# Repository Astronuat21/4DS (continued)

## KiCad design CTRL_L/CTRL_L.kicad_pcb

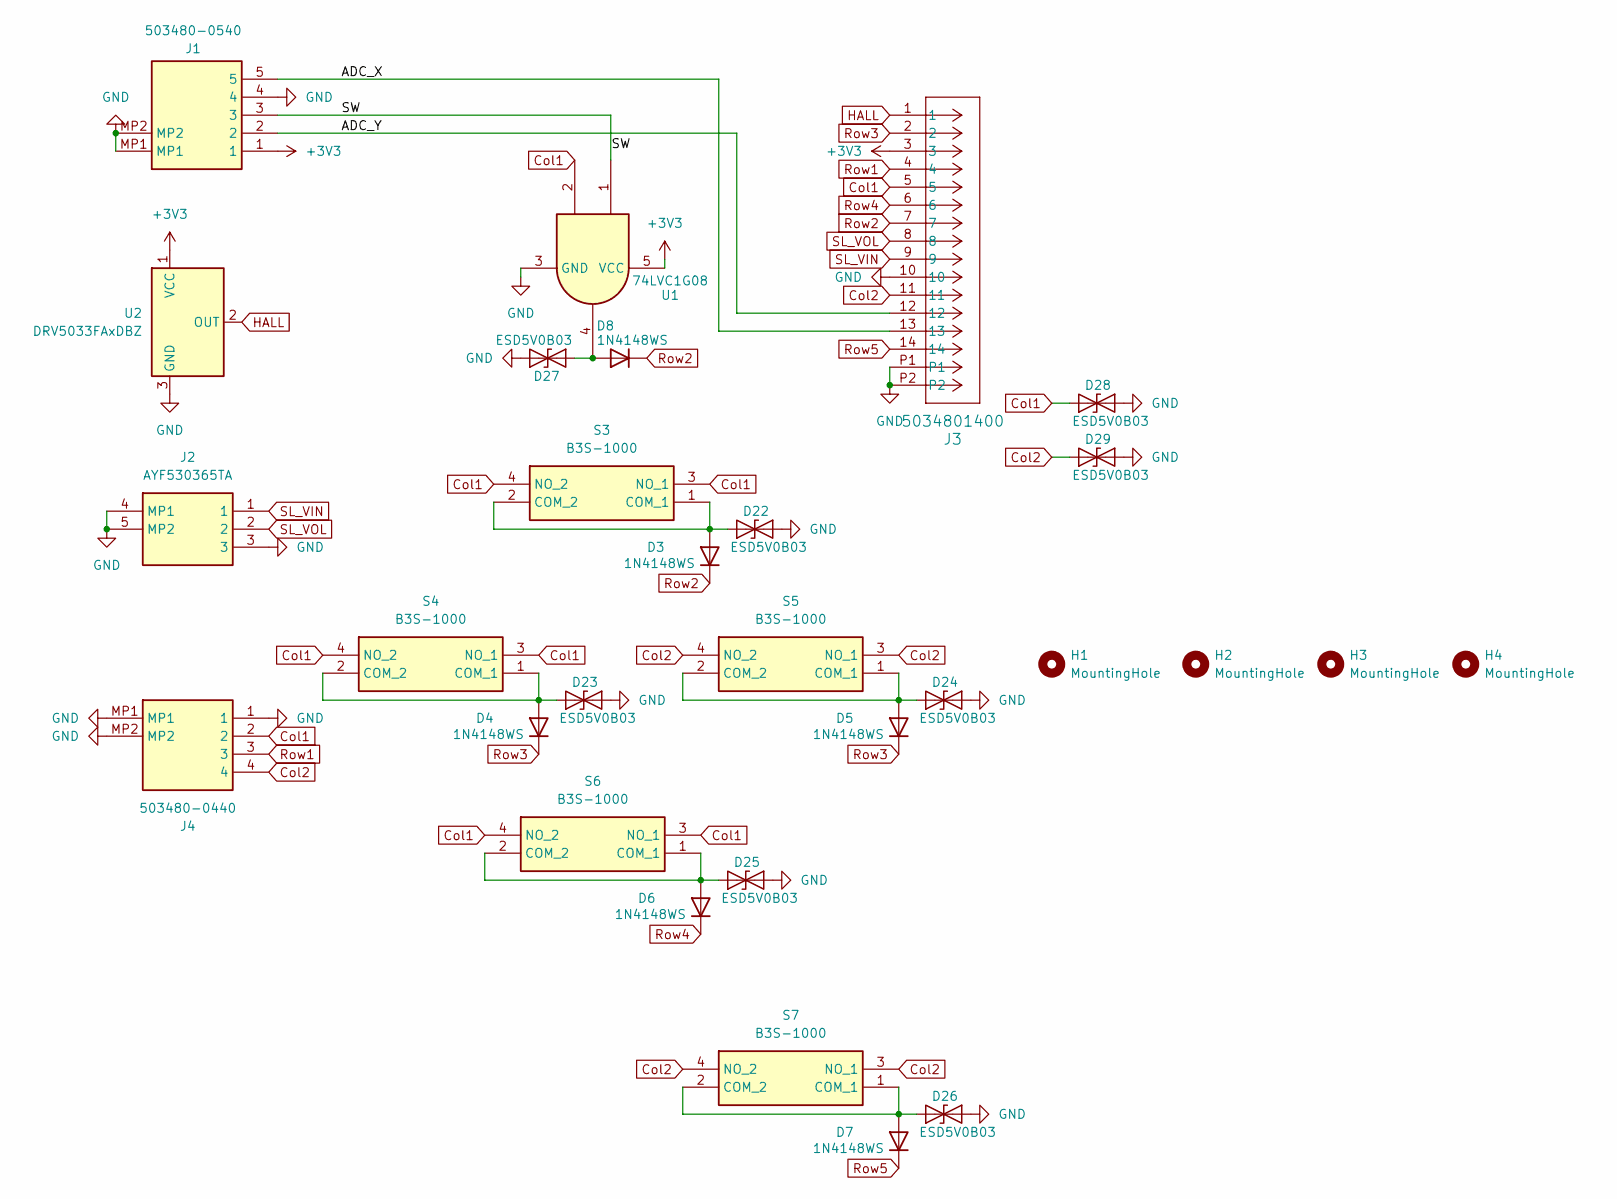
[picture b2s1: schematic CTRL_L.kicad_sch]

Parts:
D3, D4, D5, D6, D7, D8: 1N4148WS; D_SOD-323; MPN 1N4148WS; LCSC Part C917117
D22, D23, D24, D25, D26, D27, D28, D29: ESD5V0B03; D_0402_1005Metric; MPN ESD5V0B03-1006; LCSC Part C521894
H1, H2, H3, H4: MountingHole; MountingHole_2.7mm_M2.5; LCSC Part N/A
J1: 503480-0540; 5034800540; Mouser Part Number 538-503480-0540
J2: AYF530365TA; AYF530365T; Mouser Part Number 667-AYF530365TA
J3: 5034801400; MPN 5034801400; LCSC Part C505360
J4: 503480-0440; 5034800440; Mouser Part Number 538-503480-0440
S3, S4, S5, S6, S7: B3S-1000; B3S1000; Mouser Part Number 653-B3S-1000
U1: 74LVC1G08; SOT-23-5; MPN 74LVC1G08GV; LCSC Part C53185136
U2: DRV5033FAxDBZ; SOT-23; MPN DRV5033FAQDBZR; LCSC Part C2869057

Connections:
+3V3: J1.1, J3.3, U1.5 (VCC), U2.1 (VCC)
/ADC_X: J1.5, J3.13
/ADC_Y: J1.2, J3.12
/SW: J1.3, U1.1
Col1: D28.2 (A2), J3.5, J4.2, S3.3 (NO_1), S3.4 (NO_2), S4.3 (NO_1), S4.4 (NO_2), S6.3 (NO_1), S6.4 (NO_2), U1.2
Col2: D29.2 (A2), J3.11, J4.4, S5.3 (NO_1), S5.4 (NO_2), S7.3 (NO_1), S7.4 (NO_2)
GND: D22.1 (A1), D23.1 (A1), D24.1 (A1), D25.1 (A1), D26.1 (A1), D27.1 (A1), D28.1 (A1), D29.1 (A1), J1.4, J1.MP1, J1.MP2, J2.3, J2.4 (MP1), J2.5 (MP2), J3.10, J3.P1, J3.P2, J4.1, J4.MP1, J4.MP2, U1.3 (GND), U2.3 (GND)
HALL: J3.1, U2.2 (OUT)
unnamed: D3.2 (A), D22.2 (A2), S3.1 (COM_1), S3.2 (COM_2)
unnamed: D4.2 (A), D23.2 (A2), S4.1 (COM_1), S4.2 (COM_2)
unnamed: D5.2 (A), D24.2 (A2), S5.1 (COM_1), S5.2 (COM_2)
unnamed: D6.2 (A), D25.2 (A2), S6.1 (COM_1), S6.2 (COM_2)
unnamed: D7.2 (A), D26.2 (A2), S7.1 (COM_1), S7.2 (COM_2)
unnamed: D8.2 (A), D27.2 (A2), U1.4
Row1: J3.4, J4.3
Row2: D3.1 (K), D8.1 (K), J3.7
Row3: D4.1 (K), D5.1 (K), J3.2
Row4: D6.1 (K), J3.6
Row5: D7.1 (K), J3.14
SL_VIN: J2.1, J3.9
SL_VOL: J2.2, J3.8

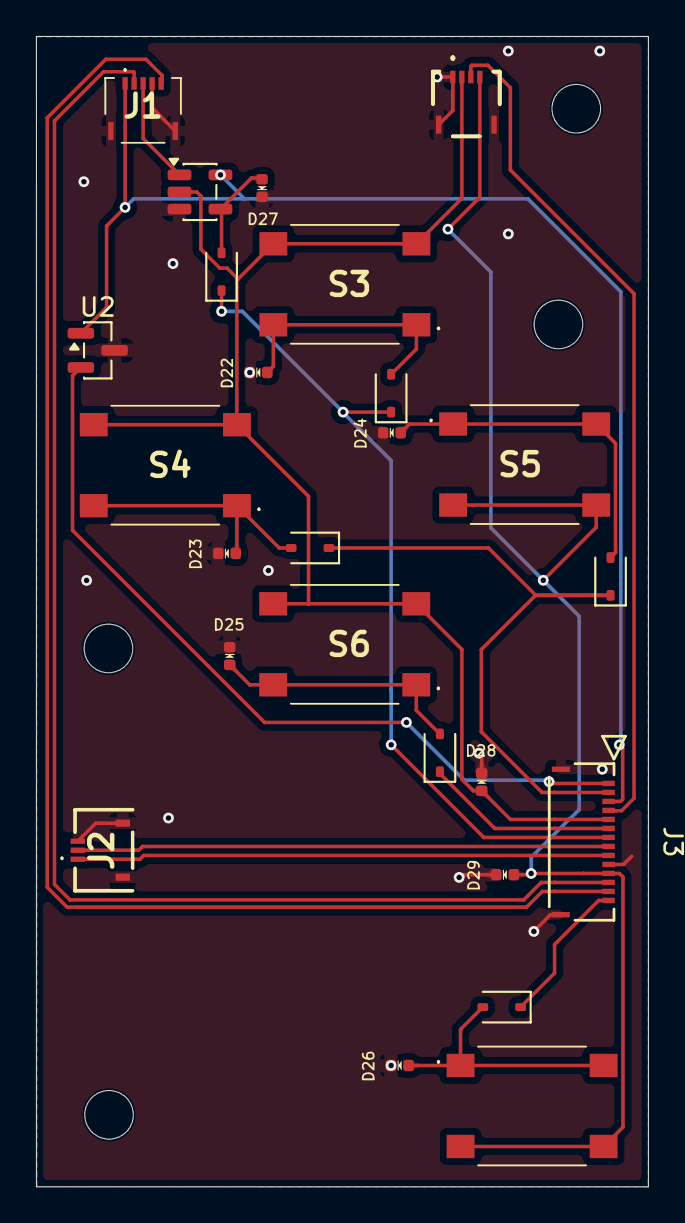
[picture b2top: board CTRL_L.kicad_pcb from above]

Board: 2 copper layers, 34.0 x 63.9 mm, 31 parts (2 on the bottom side), 21 nets.

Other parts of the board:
kibuzzard-6A186FEC: G***; kibuzzard-6A186FEC
kibuzzard-6A187131: G***; kibuzzard-6A187131

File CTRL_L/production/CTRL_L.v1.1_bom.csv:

Designator,Footprint,Quantity,Value,LCSC Part #
"D22, D23, D24, D25, D26, D27, D28, D29",0402,8,ESD5V0B03,C521894
"D3, D4, D5, D6, D7, D8",D_SOD-323,6,1N4148WS,
J2,AYF530365T,1,AYF530365TA,
J3,5034801400,1,5034801400,
J4,5034800440,1,503480-0440,
KIBUZZARD-6A186FEC,kibuzzard-6A186FEC,1,G***,
"S3, S4, S5, S6, S7",B3S1000,5,B3S-1000,
U1,SOT-23-5,1,74LVC1G08,
U2,SOT-23,1,DRV5033FAxDBZ,

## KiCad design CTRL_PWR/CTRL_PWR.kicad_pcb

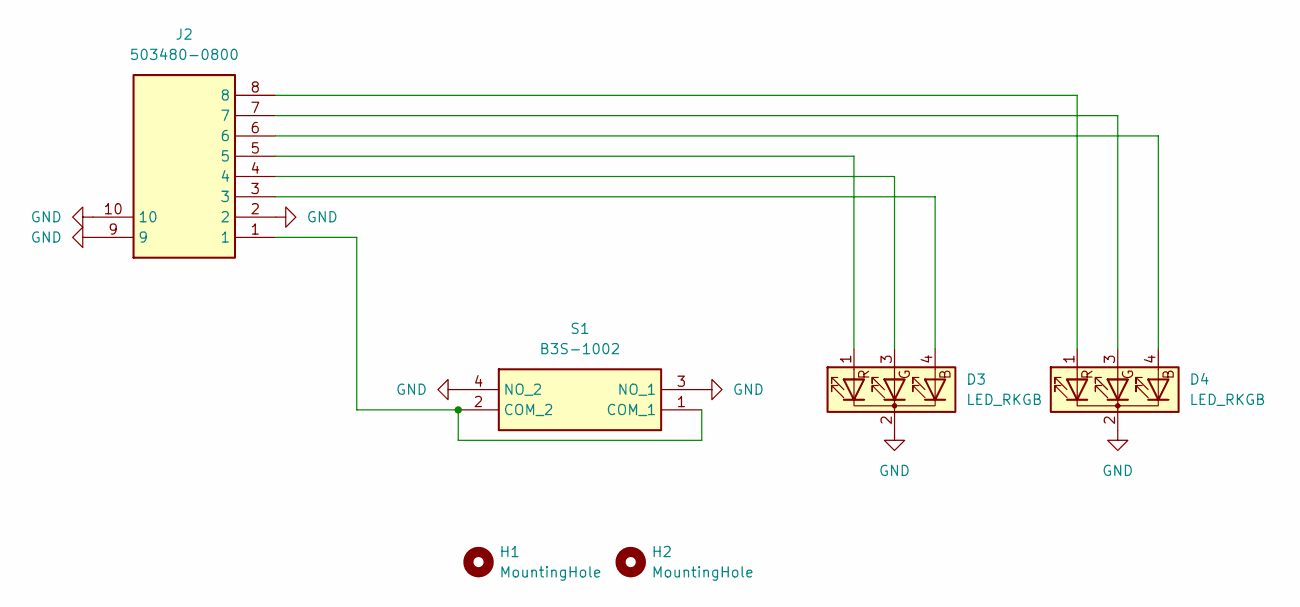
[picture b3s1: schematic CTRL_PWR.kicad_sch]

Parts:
D3, D4: LED_RKGB; LED_D5.0mm-4_RGB; MPN TJ-L5FCMXHTCSLCRGB-A5; LCSC Part C2837020
H1, H2: MountingHole; MountingHole_2.7mm_M2.5; LCSC Part N/A
J2: 503480-0800; 5034800800; Manufacturer_Part_Number 503480-0800
S1: B3S-1002; B3S1002; MPN B3S-1002; LCSC Part C2733654

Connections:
GND: D3.2 (K), D4.2 (K), J2.2, J2.9, J2.10, S1.3 (NO_1), S1.4 (NO_2)
unnamed: D3.4 (BA), J2.3
unnamed: D3.3 (GA), J2.4
unnamed: D3.1 (RA), J2.5
unnamed: D4.4 (BA), J2.6
unnamed: D4.3 (GA), J2.7
unnamed: D4.1 (RA), J2.8
unnamed: J2.1, S1.1 (COM_1), S1.2 (COM_2)

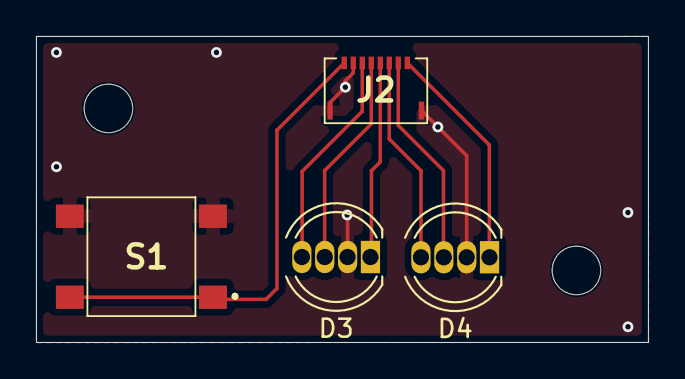
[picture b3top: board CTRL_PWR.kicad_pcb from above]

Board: 2 copper layers, 34.0 x 17.0 mm, 6 parts (0 on the bottom side), 8 nets.

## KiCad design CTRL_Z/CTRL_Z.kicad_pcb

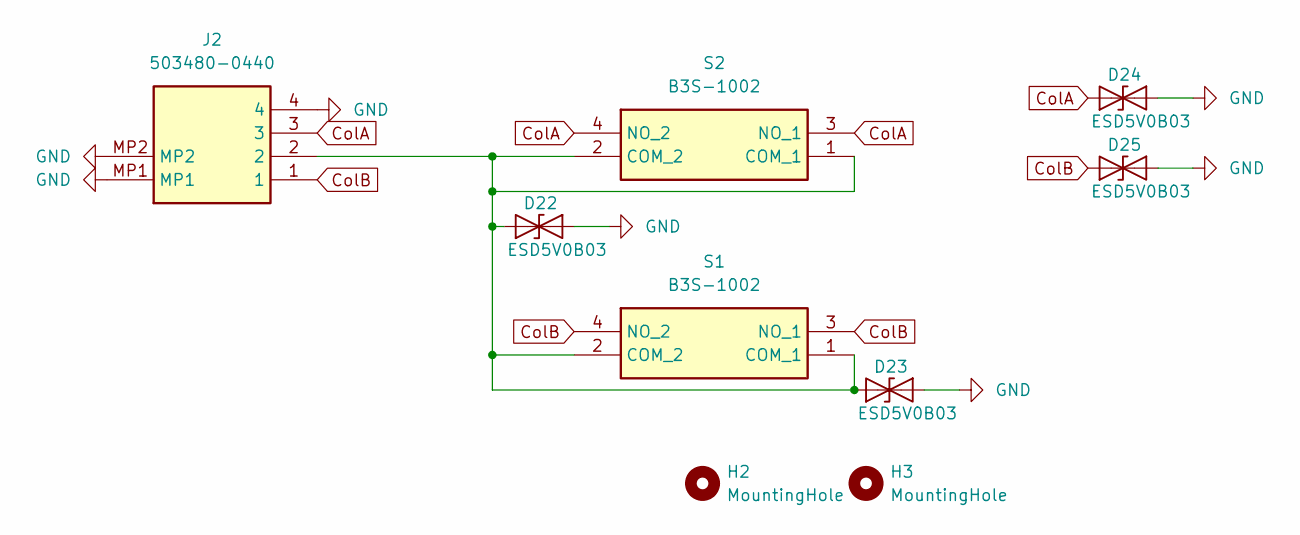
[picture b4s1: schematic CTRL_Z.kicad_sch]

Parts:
D22, D23, D24, D25: ESD5V0B03; D_0402_1005Metric; MPN ESD5V0B03-1006; LCSC Part C521894
H2, H3: MountingHole; MountingHole_2.5mm; LCSC Part N/A
J2: 503480-0440; 5034800440; Mouser Part Number 538-503480-0440
S1, S2: B3S-1002; B3S1002; Mouser Part Number 653-B3S-1002

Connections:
ColA: D24.2 (A2), J2.3, S2.3 (NO_1), S2.4 (NO_2)
ColB: D25.2 (A2), J2.1, S1.3 (NO_1), S1.4 (NO_2)
GND: D22.1 (A1), D23.1 (A1), D24.1 (A1), D25.1 (A1), J2.4, J2.MP1, J2.MP2
unnamed: D22.2 (A2), D23.2 (A2), J2.2, S1.1 (COM_1), S1.2 (COM_2), S2.1 (COM_1), S2.2 (COM_2)

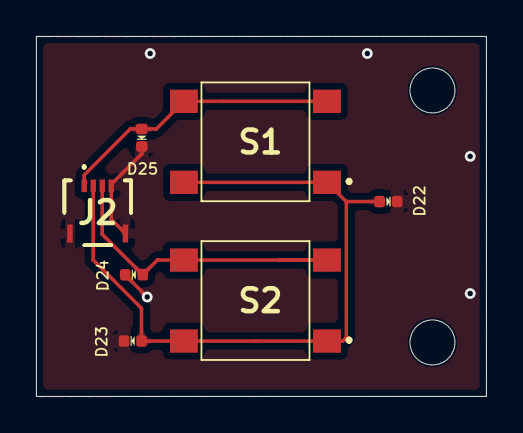
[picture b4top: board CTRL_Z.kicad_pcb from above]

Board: 2 copper layers, 25.0 x 20.0 mm, 10 parts (1 on the bottom side), 4 nets.

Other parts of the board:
kibuzzard-6A70E37C: G***; kibuzzard-6A70E37C

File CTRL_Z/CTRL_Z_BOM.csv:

"Reference","Qty","Value","Footprint","MPN","Manufacturer"
"D22,D23,D24,D25","4","ESD5V0B03","A_HDJ_Library:D_0402_1005Metric","ESD5V0B03-1006","TECH PUBLIC"
"J2","1","503480-0440","503480-0440:5034800440","5034800440","MOLEX"
"S1,S2","2","B3S-1002","B3S-1002:B3S1002","B3S-1002","OMRON"

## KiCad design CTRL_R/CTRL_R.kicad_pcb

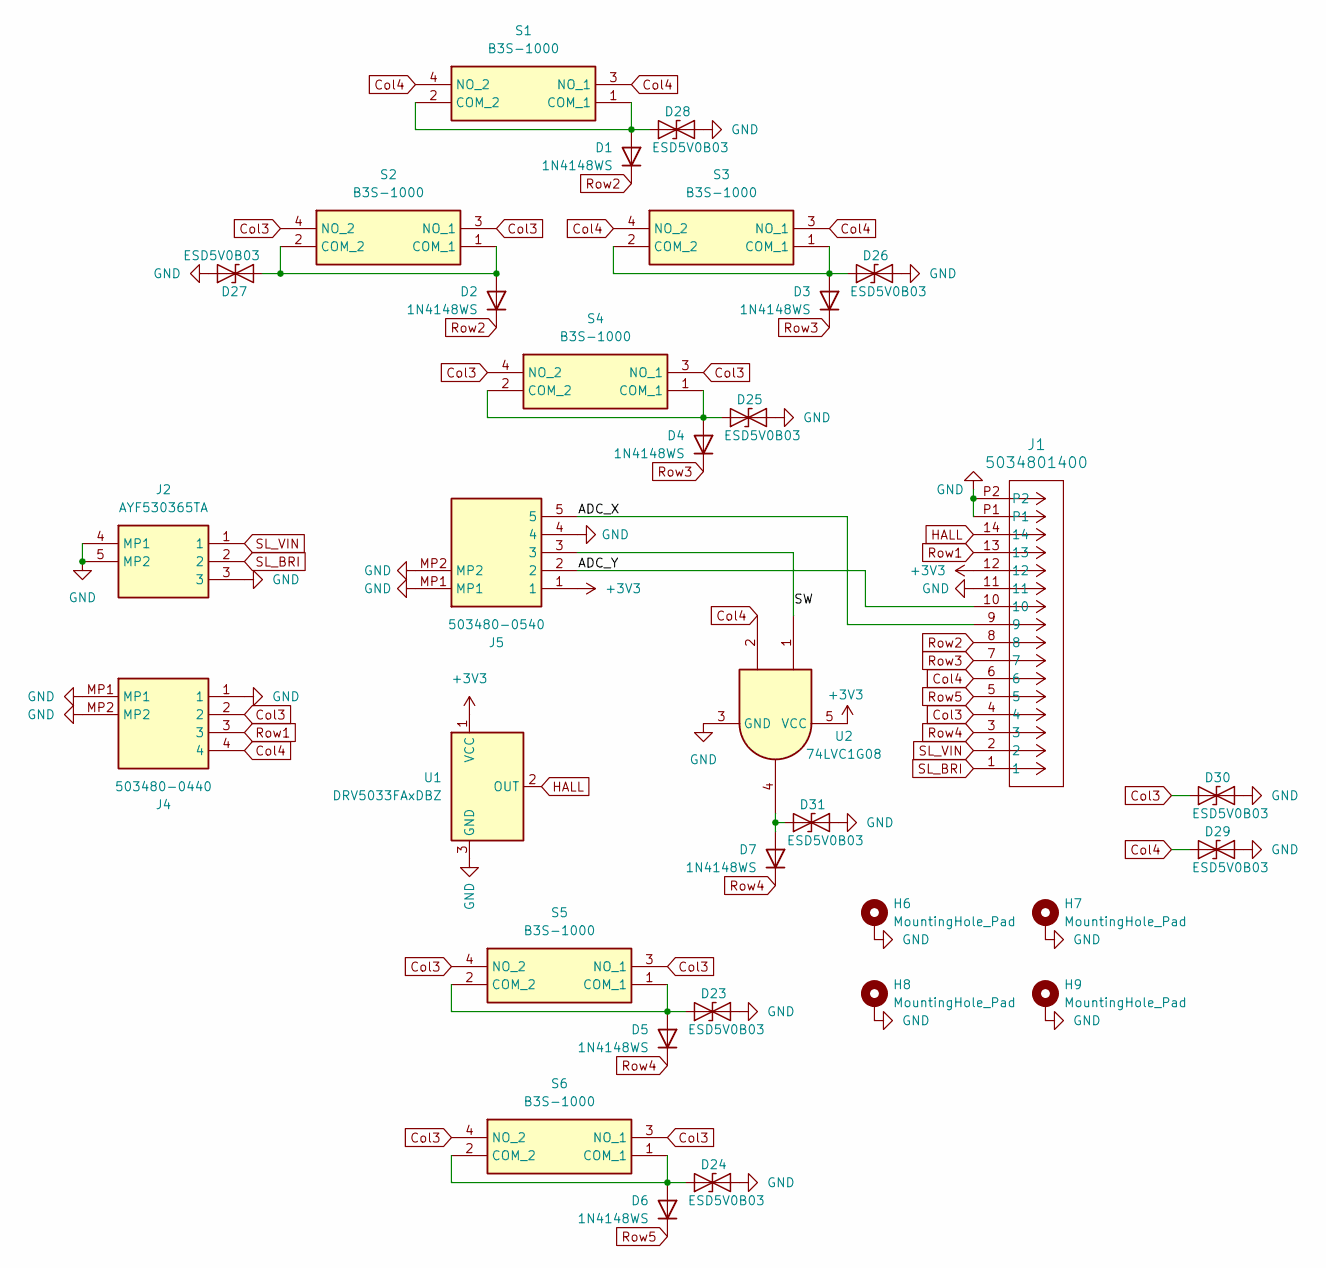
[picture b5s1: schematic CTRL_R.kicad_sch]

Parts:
D1, D2, D3, D4, D5, D6, D7: 1N4148WS; D_SOD-323; MPN 1N4148WS; LCSC Part C917117
D23, D24, D25, D26, D27, D28, D29, D30, D31: ESD5V0B03; D_0402_1005Metric; MPN ESD5V0B03-1006; LCSC Part C521894
H6, H7, H8, H9: MountingHole_Pad; MountingHole_2.7mm_M2.5_Pad; LCSC Part N/A
J1: 5034801400; MPN 5034801400; LCSC Part C505360
J2: AYF530365TA; AYF530365T; Mouser Part Number 667-AYF530365TA
J4: 503480-0440; 5034800440; Mouser Part Number 538-503480-0440
J5: 503480-0540; 5034800540; Mouser Part Number 538-503480-0540
S1, S2, S3, S4, S5, S6: B3S-1000; B3S1000; Mouser Part Number 653-B3S-1000
U1: DRV5033FAxDBZ; SOT-23; MPN DRV5033FAQDBZR; LCSC Part C2869057
U2: 74LVC1G08; SOT-23-5; MPN 74LVC1G08GV; LCSC Part C53185136

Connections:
+3V3: J1.12, J5.1, U1.1 (VCC), U2.5 (VCC)
/ADC_X: J1.9, J5.5
/ADC_Y: J1.10, J5.2
/SW: J5.3, U2.1
Col3: D30.2 (A2), J1.4, J4.2, S2.3 (NO_1), S2.4 (NO_2), S4.3 (NO_1), S4.4 (NO_2), S5.3 (NO_1), S5.4 (NO_2), S6.3 (NO_1), S6.4 (NO_2)
Col4: D29.2 (A2), J1.6, J4.4, S1.3 (NO_1), S1.4 (NO_2), S3.3 (NO_1), S3.4 (NO_2), U2.2
GND: D23.1 (A1), D24.1 (A1), D25.1 (A1), D26.1 (A1), D27.1 (A1), D28.1 (A1), D29.1 (A1), D30.1 (A1), D31.1 (A1), H6.1 (1_1), H7.1 (1_1), H8.1 (1_1), H9.1 (1_1), J1.11, J1.P1, J1.P2, J2.3, J2.4 (MP1), J2.5 (MP2), J4.1, J4.MP1, J4.MP2, J5.4, J5.MP1, J5.MP2, U1.3 (GND), U2.3 (GND)
HALL: J1.14, U1.2 (OUT)
unnamed: D1.2 (A), D28.2 (A2), S1.1 (COM_1), S1.2 (COM_2)
unnamed: D2.2 (A), D27.2 (A2), S2.1 (COM_1), S2.2 (COM_2)
unnamed: D5.2 (A), D23.2 (A2), S5.1 (COM_1), S5.2 (COM_2)
unnamed: D6.2 (A), D24.2 (A2), S6.1 (COM_1), S6.2 (COM_2)
unnamed: D4.2 (A), D25.2 (A2), S4.1 (COM_1), S4.2 (COM_2)
unnamed: D3.2 (A), D26.2 (A2), S3.1 (COM_1), S3.2 (COM_2)
unnamed: D7.2 (A), D31.2 (A2), U2.4
Row1: J1.13, J4.3
Row2: D1.1 (K), D2.1 (K), J1.8
Row3: D3.1 (K), D4.1 (K), J1.7
Row4: D5.1 (K), D7.1 (K), J1.3
Row5: D6.1 (K), J1.5
SL_BRI: J1.1, J2.2
SL_VIN: J1.2, J2.1

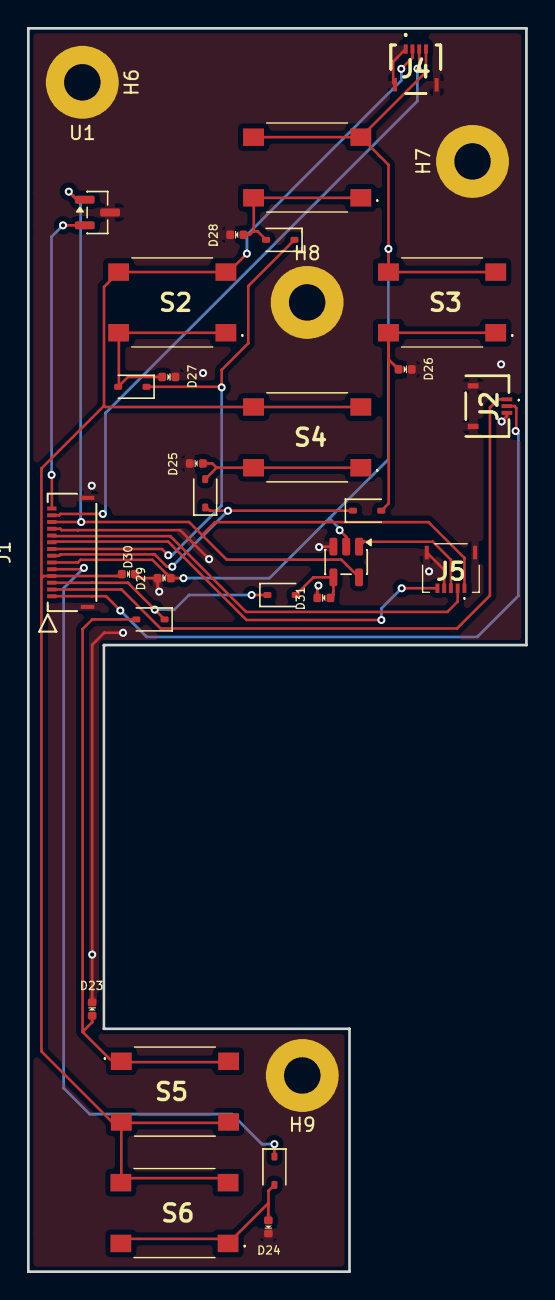
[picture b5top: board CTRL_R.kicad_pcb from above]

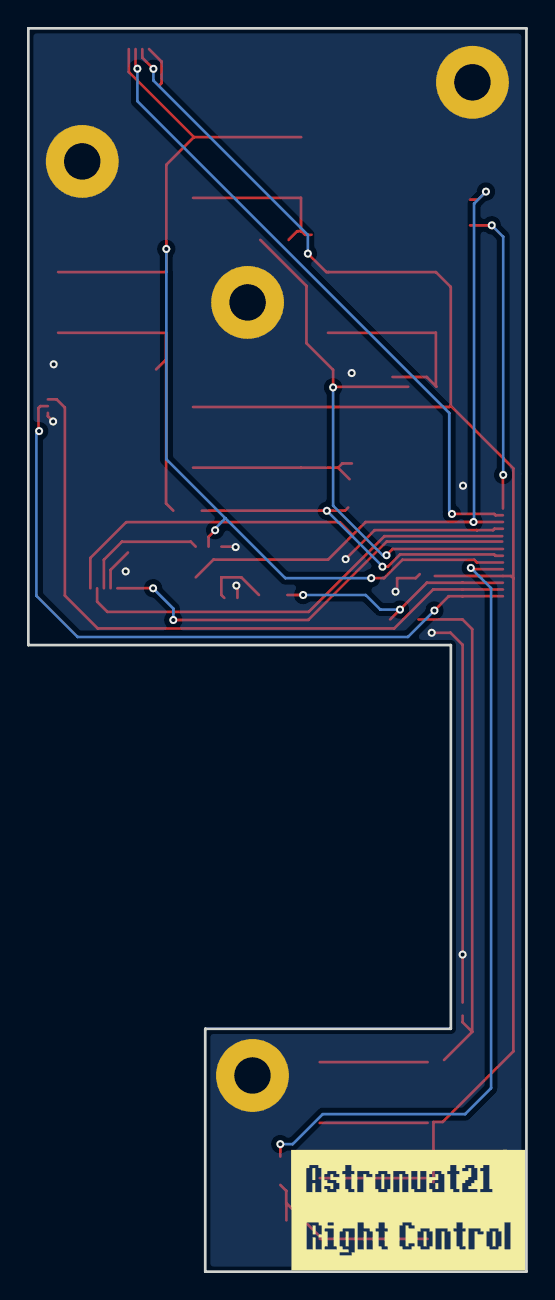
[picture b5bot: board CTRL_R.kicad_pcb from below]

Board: 2 copper layers, 36.9 x 92.2 mm, 34 parts (2 on the bottom side), 22 nets.

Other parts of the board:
kibuzzard-6A19F3B7: G***; kibuzzard-6A19F3B7
kibuzzard-6A187131: G***; kibuzzard-6A187131

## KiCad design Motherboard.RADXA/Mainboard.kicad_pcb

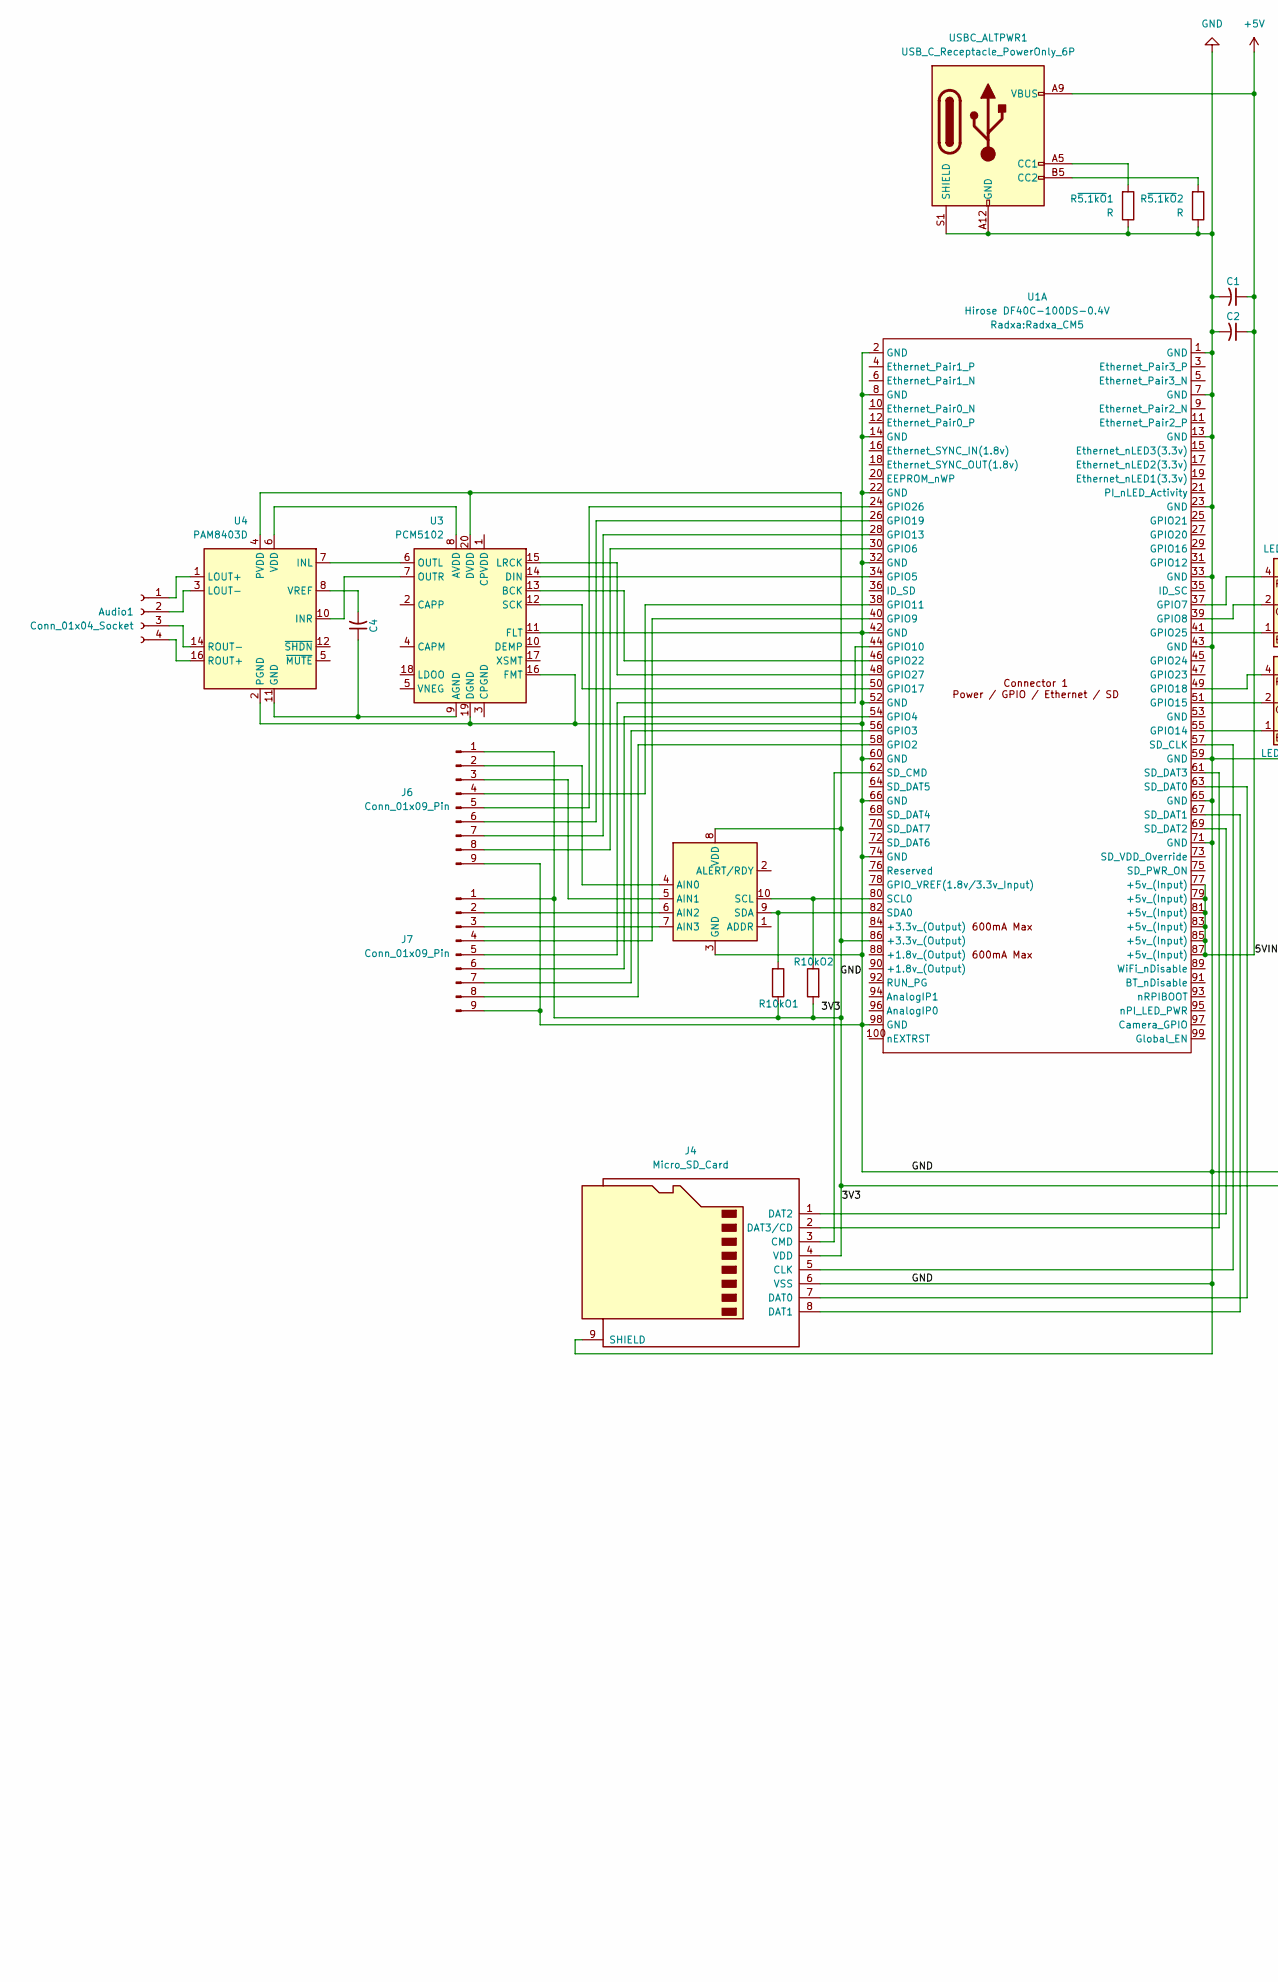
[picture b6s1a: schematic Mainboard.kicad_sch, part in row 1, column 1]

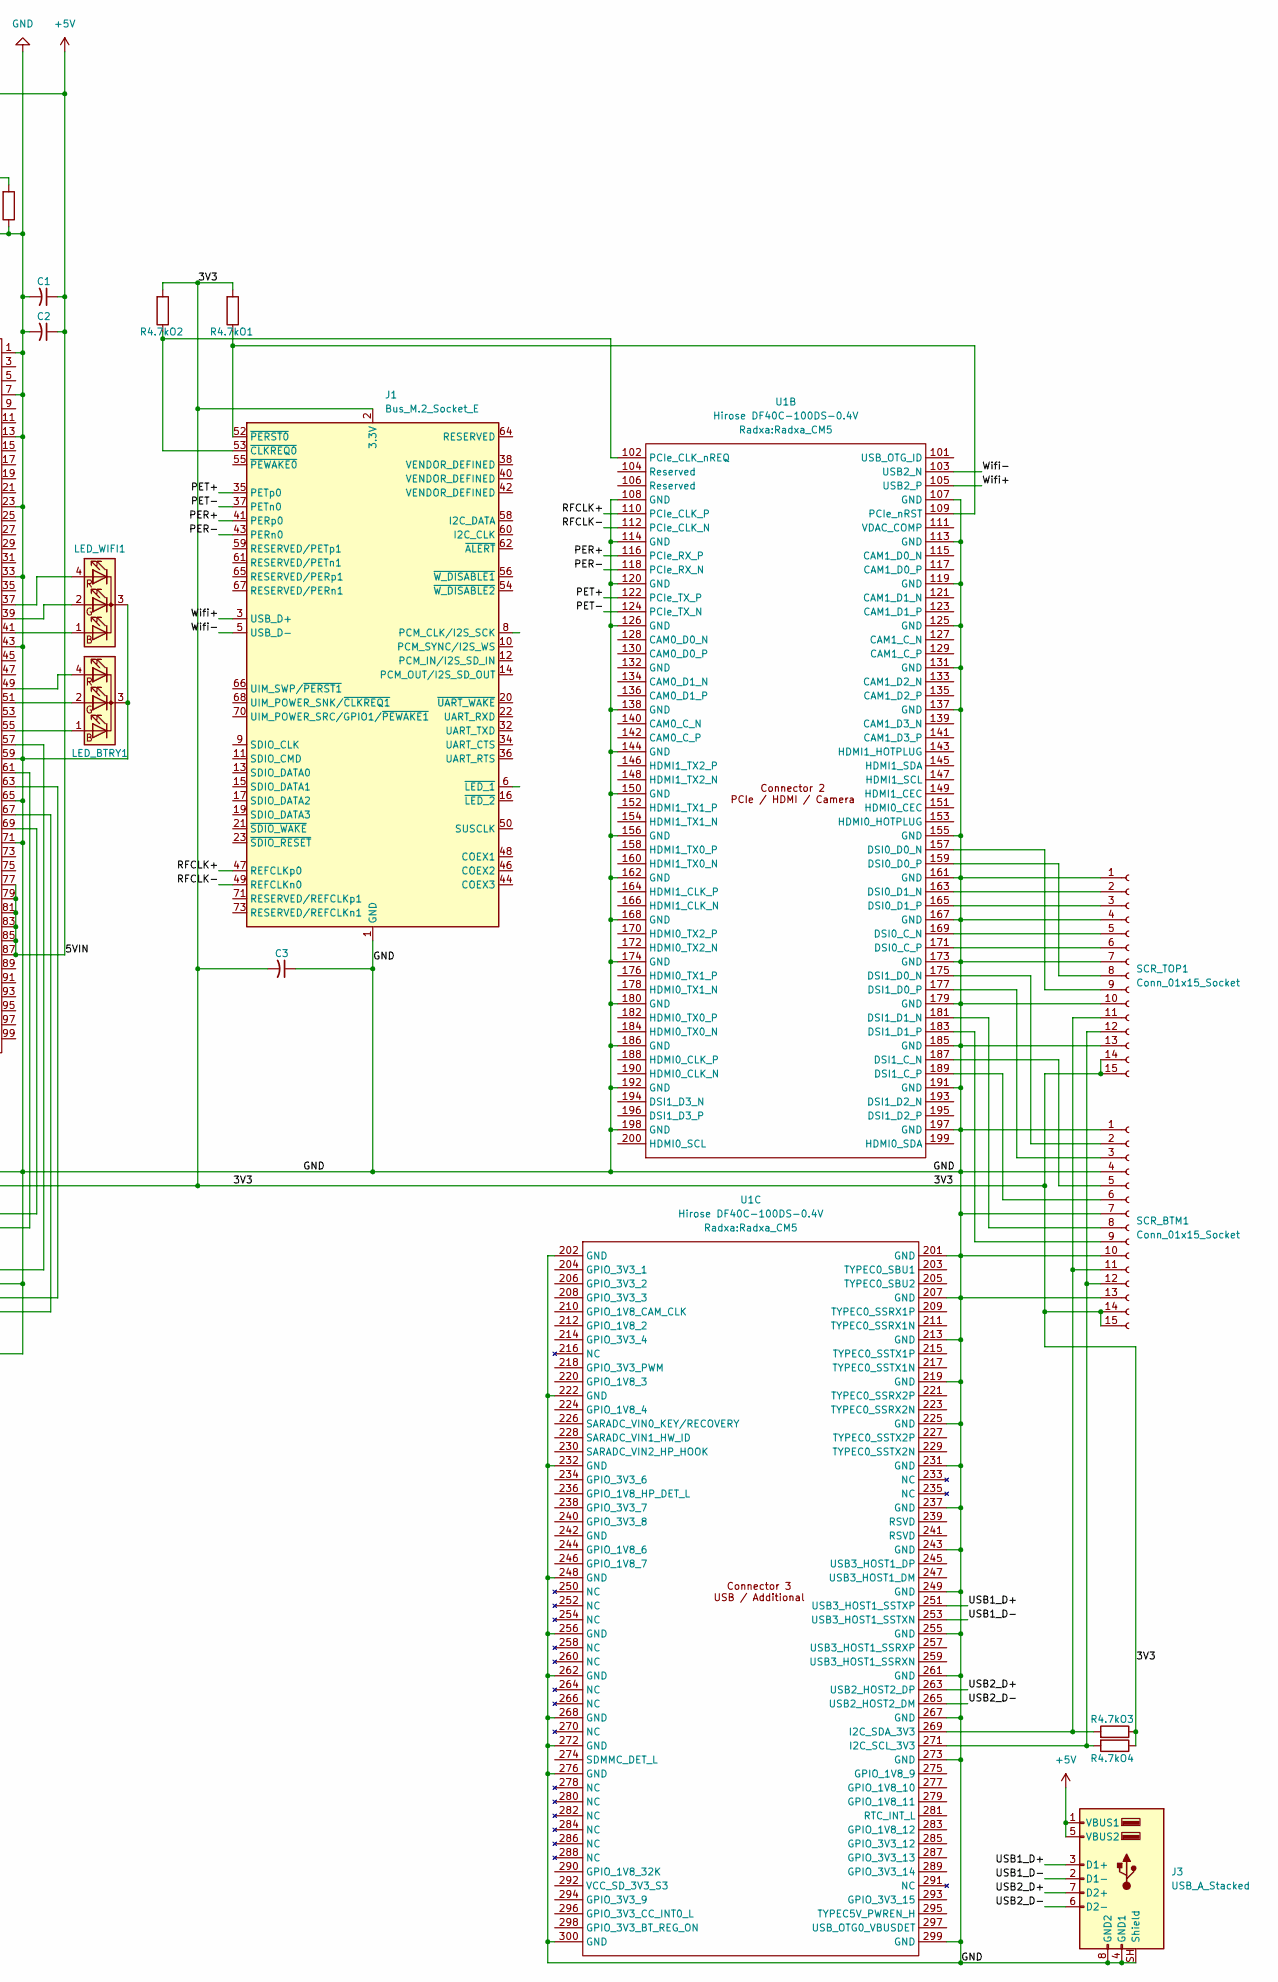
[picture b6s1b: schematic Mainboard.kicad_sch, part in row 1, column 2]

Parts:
Audio1: Conn_01x04_Socket; TE_84982-4_2Rows-04Pins-P1.0mm_Vertical
C1, C2, C3, C4: C_Small_US; C_0201_0603Metric_Pad0.64x0.40mm_HandSolder
J1: Bus_M.2_Socket_E; TE_2199230-8
J3: USB_A_Stacked; USB_A_CUI_UJ2-ADH-TH_Horizontal_Stacked
J4: Micro_SD_Card; microSD_HC_Wuerth_693072010801
J6, J7: Conn_01x09_Pin; Hirose_FH12-8S-0.5SH_1x08-1MP_P0.50mm_Horizontal
LED_BTRY1: LED_BGKR; LED_D5.0mm-4_RGB
LED_WIFI1: LED_BGKR; LED_D5.0mm-4_RGB
R4.7kO1, R4.7kO2, R4.7kO3, R4.7kO4, R10kO1, R10kO2: R; R_0603_1608Metric_Pad0.98x0.95mm_HandSolder
R~{5.1kO}1, R~{5.1kO}2: R; R_0603_1608Metric_Pad0.98x0.95mm_HandSolder
SCR_BTM1: Conn_01x15_Socket; TE_1-84953-5_1x15-1MP_P1.0mm_Horizontal
SCR_TOP1: Conn_01x15_Socket; TE_1-84953-5_1x15-1MP_P1.0mm_Horizontal
U1: Hirose DF40C-100DS-0.4V; Radxa_CM5
U2: ADS1115IDGS; TSSOP-10_3x3mm_P0.5mm
U3: PCM5102; TSSOP-20_4.4x6.5mm_P0.65mm
U4: PAM8403D; SOP-16_3.9x9.9mm_P1.27mm
USBC_ALTPWR1: USB_C_Receptacle_PowerOnly_6P; USB_C_Receptacle_GCT_USB4125-xx-x-0190_6P_TopMnt_Horizontal

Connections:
+5V: C1.1, C2.1, J3.1 (VBUS1), J3.5 (VBUS2), U1.77 (+5v_(Input)), U1.79 (+5v_(Input)), U1.81 (+5v_(Input)), U1.83 (+5v_(Input)), U1.85 (+5v_(Input)), U1.87 (+5v_(Input)), USBC_ALTPWR1.A9 (VBUS), USBC_ALTPWR1.B9 (VBUS)
/3V3: C3.2, J1.2 (3.3V), J1.4 (3.3V), J1.72 (3.3V), J1.74 (3.3V), J4.4 (VDD), J6.1, J7.1, R4.7kO1.2, R4.7kO2.2, R4.7kO3.1, R4.7kO4.1, R10kO1.1, R10kO2.2, SCR_BTM1.14, SCR_BTM1.15, SCR_TOP1.14, SCR_TOP1.15, U1.86 (+3.3v_(Output)), U2.8 (VDD), U3.20 (DVDD), U4.4 (PVDD), U4.13 (PVDD)
/PER+: J1.41 (PERp0), U1.116 (PCIe_RX_P)
/PER-: J1.43 (PERn0), U1.118 (PCIe_RX_N)
/PET+: J1.35 (PETp0), U1.122 (PCIe_TX_P)
/PET-: J1.37 (PETn0), U1.124 (PCIe_TX_N)
/RFCLK+: J1.47 (REFCLKp0), U1.110 (PCIe_CLK_P)
/RFCLK-: J1.49 (REFCLKn0), U1.112 (PCIe_CLK_N)
/USB1_D+: J3.3 (D1+), U1.251 (USB3_HOST1_SSTXP)
/USB1_D-: J3.2 (D1-), U1.253 (USB3_HOST1_SSTXN)
/USB2_D+: J3.7 (D2+), U1.263 (USB2_HOST2_DP)
/USB2_D-: J3.6 (D2-), U1.265 (USB2_HOST2_DM)
/Wifi+: J1.3 (USB_D+), U1.105 (USB2_P)
/Wifi-: J1.5 (USB_D-), U1.103 (USB2_N)
GND: C1.2, C2.2, C3.1, J1.1 (GND), J1.7 (GND), J1.18 (GND), J1.33 (GND), J1.39 (GND), J1.45 (GND), J1.51 (GND), J1.57 (GND), J1.63 (GND), J1.69 (GND), J1.75 (GND), J3.4 (GND1), J3.8 (GND2), J3.SH (Shield), J4.6 (VSS), J4.9 (SHIELD), J6.9, J7.9, LED_BTRY1.3 (K), LED_WIFI1.3 (K), R~{5.1kO}1.1, R~{5.1kO}2.1, SCR_BTM1.1, SCR_BTM1.4, SCR_BTM1.7, SCR_BTM1.10, SCR_BTM1.13, SCR_TOP1.1, SCR_TOP1.4, SCR_TOP1.7, SCR_TOP1.10, SCR_TOP1.13, U1.1 (GND), U1.2 (GND), U1.7 (GND), U1.8 (GND), U1.13 (GND), U1.14 (GND), U1.22 (GND), U1.23 (GND), U1.32 (GND), U1.33 (GND), U1.42 (GND), U1.43 (GND), U1.52 (GND), U1.59 (GND), U1.60 (GND), U1.65 (GND), U1.66 (GND), U1.71 (GND), U1.74 (GND), U1.98 (GND), U1.107 (GND), U1.108 (GND), U1.113 (GND), U1.114 (GND), U1.119 (GND), U1.120 (GND), U1.125 (GND), U1.126 (GND), U1.131 (GND), U1.137 (GND), U1.138 (GND), U1.144 (GND), U1.150 (GND), U1.155 (GND), U1.156 (GND), U1.161 (GND), U1.162 (GND), U1.167 (GND), U1.168 (GND), U1.173 (GND), U1.174 (GND), U1.179 (GND), U1.180 (GND), U1.185 (GND), U1.186 (GND), U1.191 (GND), U1.192 (GND), U1.197 (GND), U1.198 (GND), U1.201 (GND), U1.202 (GND), U1.207 (GND), U1.213 (GND), U1.219 (GND), U1.222 (GND), U1.225 (GND), U1.231 (GND), U1.232 (GND), U1.237 (GND), U1.243 (GND), U1.248 (GND), U1.249 (GND), U1.255 (GND), U1.256 (GND), U1.261 (GND), U1.262 (GND), U1.267 (GND), U1.268 (GND), U1.272 (GND), U1.273 (GND), U1.276 (GND), U1.299 (GND), U1.300 (GND), U2.3 (GND), U3.11 (FLT), U3.16 (FMT), U3.19 (DGND), U4.2 (PGND), U4.15 (PGND), USBC_ALTPWR1.A12 (GND), USBC_ALTPWR1.B12 (GND), USBC_ALTPWR1.S1 (SHIELD)
unnamed: Audio1.1, U4.1 (LOUT+)
unnamed: Audio1.2, U4.3 (LOUT-)
unnamed: Audio1.3, U4.14 (ROUT-)
unnamed: Audio1.4, U4.16 (ROUT+)
unnamed: J1.53 (~CLKREQ0), R4.7kO2.1, U1.102 (PCIe_CLK_nREQ)
unnamed: J1.52 (~PERST0), R4.7kO1.1, U1.109 (PCIe_nRST)
unnamed: J4.5 (CLK), U1.57 (SD_CLK)
unnamed: J4.3 (CMD), U1.62 (SD_CMD)
unnamed: J4.7 (DAT0), U1.63 (SD_DAT0)
unnamed: J4.8 (DAT1), U1.67 (SD_DAT1)
unnamed: J4.1 (DAT2), U1.69 (SD_DAT2)
unnamed: J4.2 (DAT3/CD), U1.61 (SD_DAT3)
unnamed: J6.2, U2.4 (AIN0)
unnamed: J6.3, U2.5 (AIN1)
unnamed: J6.4, U1.38 (GPIO11)
unnamed: J6.5, U1.24 (GPIO26)
unnamed: J6.6, U1.26 (GPIO19)
unnamed: J6.7, U1.28 (GPIO13)
unnamed: J6.8, U1.30 (GPIO6)
unnamed: J7.2, U2.6 (AIN2)
unnamed: J7.3, U2.7 (AIN3)
unnamed: J7.4, U1.40 (GPIO9)
unnamed: J7.5, U1.44 (GPIO10)
unnamed: J7.6, U1.54 (GPIO4)
unnamed: J7.7, U1.56 (GPIO3)
unnamed: J7.8, U1.58 (GPIO2)
unnamed: LED_BTRY1.1 (BA), U1.55 (GPIO14)
unnamed: LED_BTRY1.2 (GA), U1.51 (GPIO15)
unnamed: LED_BTRY1.4 (RA), U1.49 (GPIO18)
unnamed: LED_WIFI1.1 (BA), U1.41 (GPIO25)
unnamed: LED_WIFI1.2 (GA), U1.39 (GPIO8)
unnamed: LED_WIFI1.4 (RA), U1.37 (GPIO7)
unnamed: SCR_BTM1.2, U1.175 (DSI1_D0_N)
unnamed: SCR_BTM1.3, U1.177 (DSI1_D0_P)
unnamed: SCR_BTM1.5, U1.187 (DSI1_C_N)
unnamed: SCR_BTM1.6, U1.189 (DSI1_C_P)
unnamed: SCR_BTM1.8, U1.181 (DSI1_D1_N)
unnamed: SCR_BTM1.9, U1.183 (DSI1_D1_P)
unnamed: R4.7kO3.2, SCR_BTM1.11, SCR_TOP1.11, U1.269 (I2C_SDA_3V3)
unnamed: R4.7kO4.2, SCR_BTM1.12, SCR_TOP1.12, U1.271 (I2C_SCL_3V3)
unnamed: SCR_TOP1.2, U1.163 (DSI0_D1_N)
unnamed: SCR_TOP1.3, U1.165 (DSI0_D1_P)
unnamed: SCR_TOP1.5, U1.169 (DSI0_C_N)
unnamed: SCR_TOP1.6, U1.171 (DSI0_C_P)
unnamed: SCR_TOP1.8, U1.159 (DSI0_D0_P)
unnamed: SCR_TOP1.9, U1.157 (DSI0_D0_N)
unnamed: U1.34 (GPIO5), U3.14 (DIN)
unnamed: U1.50 (GPIO17), U3.12 (SCK)
unnamed: U1.46 (GPIO22), U3.13 (BCK)
unnamed: U1.48 (GPIO27), U3.15 (LRCK)
unnamed: R10kO2.1, U1.80 (SCL0), U2.10 (SCL)
unnamed: R10kO1.2, U1.82 (SDA0), U2.9 (SDA)
unnamed: C4.1, U3.9 (AGND), U4.11 (GND)
unnamed: U3.8 (AVDD), U4.6 (VDD)
unnamed: U3.6 (OUTL), U4.7 (INL)
unnamed: U3.7 (OUTR), U4.10 (INR)
unnamed: C4.2, U4.8 (VREF)
unnamed: R~{5.1kO}1.2, USBC_ALTPWR1.A5 (CC1)
unnamed: R~{5.1kO}2.2, USBC_ALTPWR1.B5 (CC2)

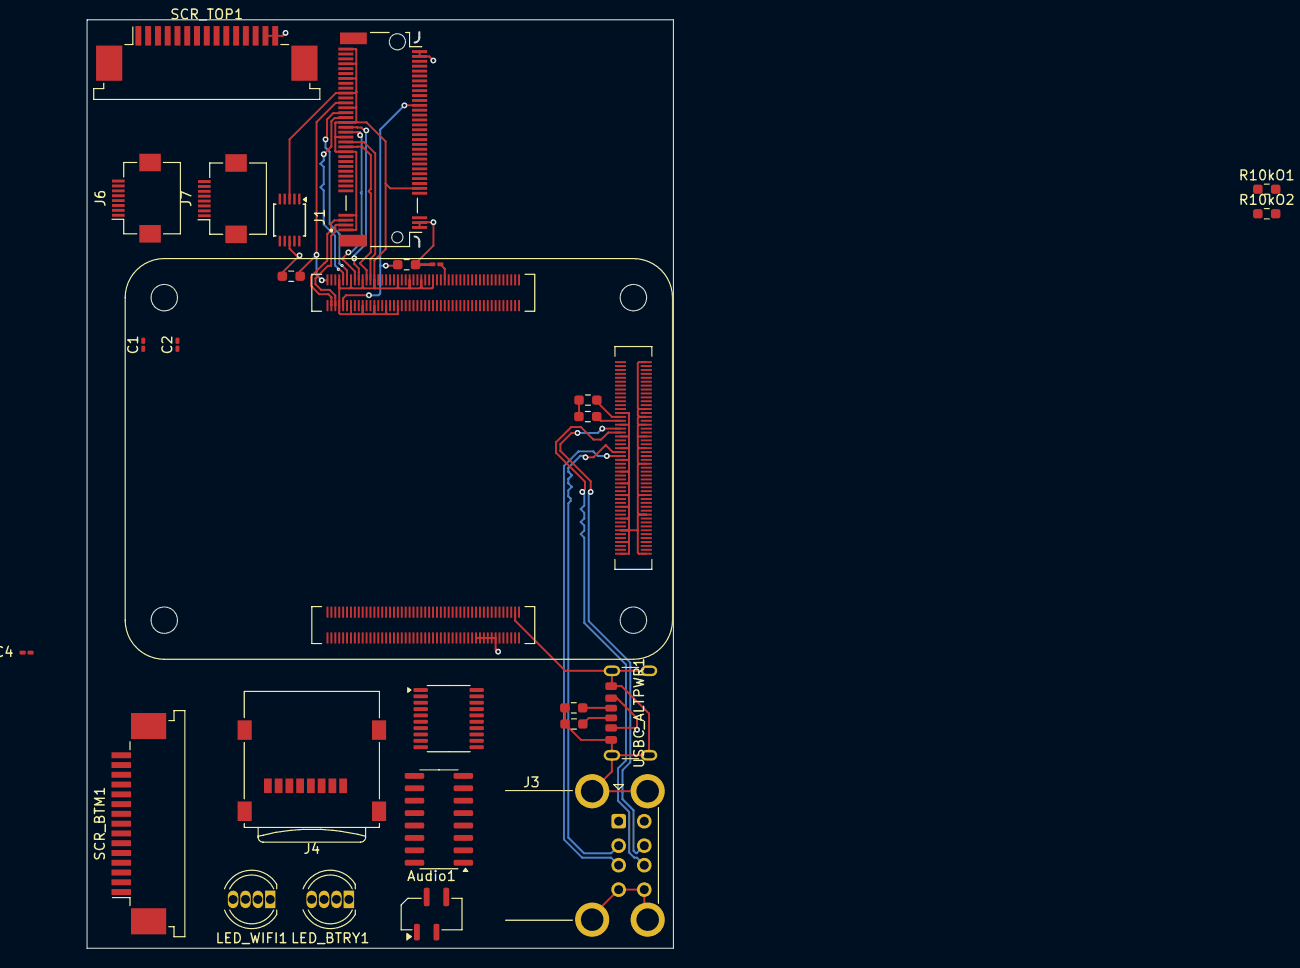
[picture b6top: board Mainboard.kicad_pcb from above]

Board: 4 copper layers, 60.0 x 95.0 mm, 27 parts (0 on the bottom side), 74 nets.

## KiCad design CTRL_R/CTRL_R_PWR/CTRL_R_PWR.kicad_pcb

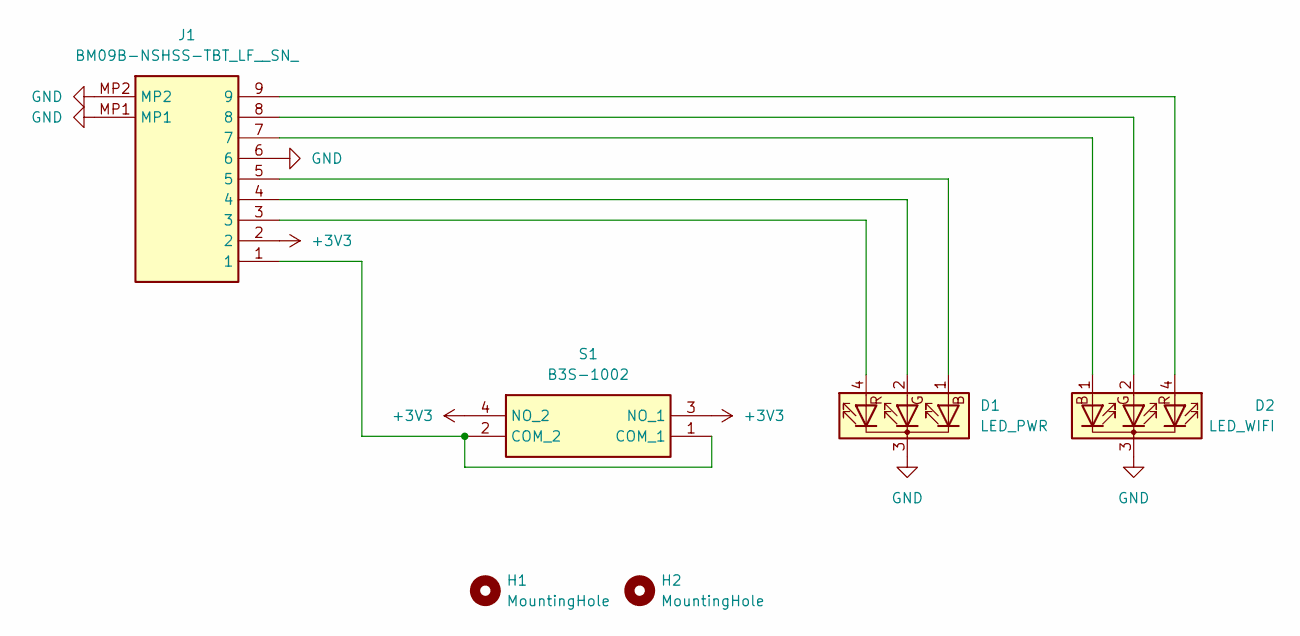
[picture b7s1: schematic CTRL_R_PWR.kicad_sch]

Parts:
D1: LED_PWR; LED_D5.0mm-4_RGB
D2: LED_WIFI; LED_D5.0mm-4_RGB
H1, H2: MountingHole; MountingHole_2.7mm_M2.5
J1: BM09B-NSHSS-TBT_LF__SN_; BM09BNSHSSTBTLFSN; Manufacturer_Part_Number BM09B-NSHSS-TBT(LF)(SN)
S1: B3S-1002; B3S1002; Mouser Part Number 653-B3S-1002

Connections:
+3V3: J1.2, S1.3 (NO_1), S1.4 (NO_2)
GND: D1.3 (K), D2.3 (K), J1.6, J1.MP1, J1.MP2
unnamed: D1.1 (BA), J1.5
unnamed: D1.2 (GA), J1.4
unnamed: D1.4 (RA), J1.3
unnamed: D2.1 (BA), J1.7
unnamed: D2.2 (GA), J1.8
unnamed: D2.4 (RA), J1.9
unnamed: J1.1, S1.1 (COM_1), S1.2 (COM_2)

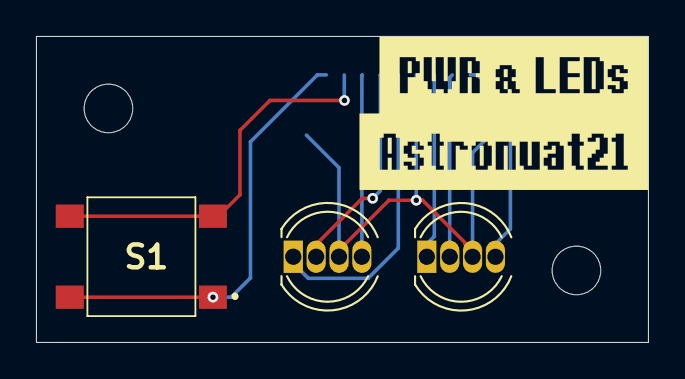
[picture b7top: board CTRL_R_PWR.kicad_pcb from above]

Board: 2 copper layers, 34.0 x 17.0 mm, 8 parts (1 on the bottom side), 9 nets.

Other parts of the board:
kibuzzard-6A2CA9F9: G***; kibuzzard-6A2CA9F9
kibuzzard-6A2CAA19: G***; kibuzzard-6A2CAA19
